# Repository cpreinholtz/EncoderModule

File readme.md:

# Overview - Dorthy - Digital Rotary Encoder based Teensy Synth
This repo contains several PCB designs and teensy firmware for building a digital sythesiser.

**Directory structure:**
* cad (empty...)
* doc (mostly datasheets and links to research sources)
* firmware (arduino sketches)
* hardware (eagle projects)
* production (gerber zips)
* simulation (empty...)

**PCBs (see detailed descriptions below)**
* **R**otary **E**ncoder **E**xpander **M**odule (REEM)
* **G**round **I**solated **M**idi **I**nput Module (GIMI)
* **D**igital **R**otary Encoder **T**eensy S**y**nth (DRTY / DORTHY)

## Rotary Encoder Expander Module (REEM)

### Overview

This module is meant to be an expandable way to attach many rotary encoders to a single i2c master.  The idea is that it can be used in creating a nice user interface for a synthesizer.  This project is meant to be small, to keep manufacturing costs down, but also expandable so that multiple of these can be connected together to make a large io pannel. Currently limited to 8 modules or 64 knobs based on the io expander chip used.

### Hardare Features

* Voltage input 1.8 — 5.5 V
* Optional pullups on SCL and SDA, do not pupulate by default,  should be pulled up on master side.
* Chainable design, simply connect modules using the ribbon cable connectors. (VCC, GND, SCL, SDA).
* 3 address pins per chip allow up to 8 unique addresses.  
 * **The address pins are floating by default and must be tied to vcc or ground by shorting one of the two 0805 resitor pads per pin**

### Future Considerations
* If you want chainable interupts, its probably possible, especially with more io lines on the chips
* it may be nice to someday take advantage of the switches built into the encoders, but i thought i would skip for now
* Optional hardware filter circuits for each encoder might improve performance but would mean more soldering
* Instead of an encoder, We could allow switches or buttons in the same form factor.
* Consider a form factor that fits with eurorack standards.
 * The Eurorack format calls for modules of 128.5mm (slightly over 5") height. Horizontal width is measured in "horizontal pitch", where 1 HP = 5.08mm (exactly 0.2").  This is larger than eagle free can build and fab houses may charge more 
* I wonder if it would be cheaper to use JST connectors for board to board connections.  See adafruit Trellis for example.

## **G**round **I**solated **M**idi **I**nput Module (GIMI)

### 

### Overview
Classic octocoupler used for midi digitization for arduino or similar controllers.

***Warning ***
In rev 1 of producing this baord the M4 and M5 pin labels were swapped on the silkscreen.  Refer to the schematic and drawings, not the silkscreen.

### Hardare Features
* reverse polarity protection diode.
* midi in uses octocoupler preventing ground loops.  
* RX pullup does not need to be 5v.  Can be tied to 3v3, or whatever voltage the controller needs.
* Jumper for quickly disconnecting RX from the circuit.  For re-programming certain controllers Rx may need to be floating.

### Future Considerations
* It would be pretty easy to add midi through and/or midi out at some point.
* It may be nice to get board mount midi connectors at some point.
* It may be nice to start using a standard cable (like JST SH or JST PH...) rather than the 100mil pitch headers I put on.

## Dorthy Teensy Synth (work in progress)
Designed around a teensy microcontroller and some other hardware modules.  Utilizes the teensy audio libraries and some custom firmware.

### Playing the Synth
Instructions and features tbd.

## Dorthy Teensy Synth Hardare 
Take a teensy, slap 64 knobs and 16 buttons onto it, make it midi compatable and make some music

#### BOM
* 1x Teensy microcontroller, at least Rev 3.5 reccomended.
* 1x Midi in GIMI module (hardware/midi_in)
* 8x REEM modules(hardware/MultiEncoder)
* 2x large capacitors for stereo audio out, simple bypass cap to bring it to 0v centered.
* LCD display? tbd
* trellis? https://www.adafruit.com/product/3954

#### Hardware Pinouts
TBD

## Dorthy Teensy Synth Firmware
This synth will make heavy use of the teensy audio libraries and other goodies found all over the web.  Special thanks to all the contributors!

#### Firmware Detailed Descriptions (Requirments...)
* Polled processes: knobs(>100Hz), capacitive touch pads(100Hz?), midi RX(Every loop), Trellis (100Hz?), Clock Monitor(Every Loop), Touchscreen(100Hz?)
* While polling, if something is found that requires updates, the dispatcher class is called.
* When called the dispatcher will perform one or more actions such as modifying the voices or other synth parameters, and updating the display.
* The synth itself will have N voices, each with its own oscilators, LFOs?, amplitude envelope, filter and filter envelope.
* The synth will then combine all voices and send them through an effects signal chain containing delay, reverb, bitcrush, etc.
* The synth will respond to pitch bending and modwheel messages.
* The synth will be able to store up to M "note on" messages at a time, and will use the LAST N notes on the voices, upon notoffs it will go back through the list in revers chronological order.

#### Firmware Immediate Todo List
* Test what happens if the SetScalers function is passed a max smaler than min, hopefully it just reverses the knob polarity, that would be sweet
* Rewrite Midi function so that it does not take 50 ms to exxecute...
* Figure out why polyphonic note off does not often continue the release envelope if another note is hit.

#### Firmware Future Considerations
* It would be nice to have a good sequencer in the future, (keep this in mind when writing the dispatcher and voice controls)  consider things like kbd play / stack live 
* It would be nice to have a built in drum machine in the future.
* It would be nice to have the ability to save patches.  (make settings easy to get / set)
* It would be nice to be able to swap LFOs from incremental clk sync to continuous bpm sweeps.  this requires some back and forth from dispatcher to clk and lfo.
* It would be nice to be able to swap from re-triggering envelopes on each additional key to using one envelop for all voices(more smooth /legatto)

#### Firmware Enviromental setup
All you should need is arduino IDE with the teensy 3.6 board installed.
Teensy 1.53 seems to work much faster than the latest versions, Note to self: I have a copy of the 1.53 installer on my google drive main folder "installexes.rar" 
Arduino 1.8.13 works with this version of Teensy, I think I had issues with 1.8.16 and that teensy version.

#### Firmware Dependencies
must have https://github.com/cpreinholtz/midi.git   installed in Docs/Arduino/Libraries, look at the dates, its being developed in tandem but for now the latest woriking commit is 7a53122

#### Firmware Limitations
TBD

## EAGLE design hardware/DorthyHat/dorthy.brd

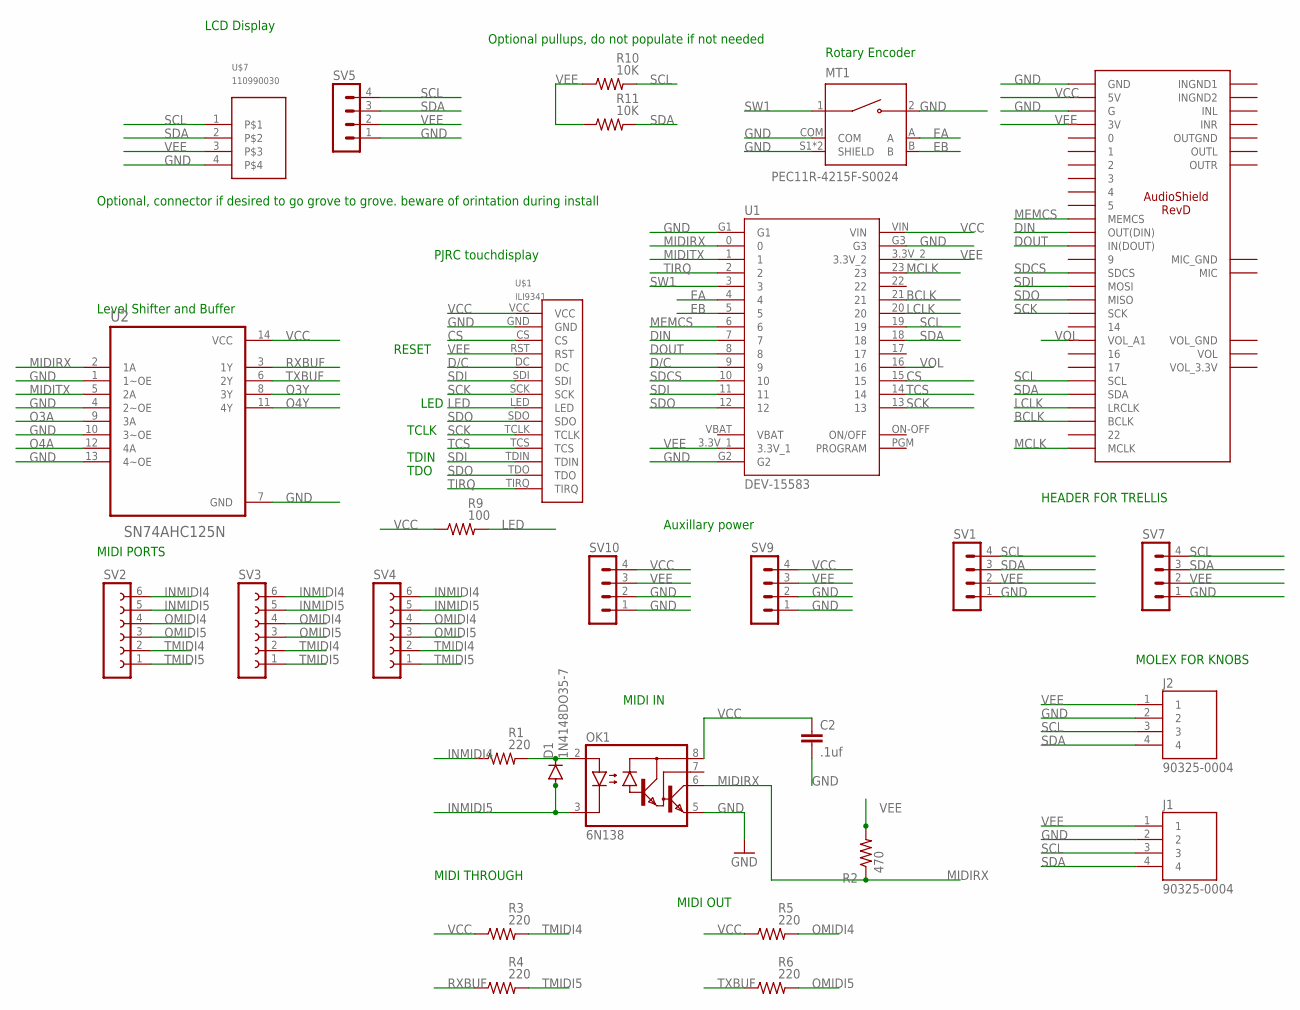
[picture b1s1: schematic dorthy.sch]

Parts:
C2: .1uf; C5B3.5
D1: 1N4148DO35-7; DO35-7
J1, J2: 90325-0004; MOLEX_90325-0004
MT1: PEC11R-4215F-S0024; XDCR_PEC11R-4215F-S0024
OK1: 6N138; DIL08
R1, R3, R4, R5, R6: 220; 0207/10
R2: 470; 0207/10
R9: 100; 0207/10
R10, R11: 10K; 0207/10
SV1, SV5, SV7, SV9, SV10: MA04-1
SV2, SV3, SV4: FE06-1; FE06
U1: DEV-15583; MODULE_DEV-15583
U2: SN74AHC125N; DIP794W45P254L1969H508Q14
U$1: ILI9341
U$2: AUDIOSHIELD-REVD
U$7: 110990030; 110990030-VERTICAL-GROVE-CONNECTOR

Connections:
BCLK: U1.21, U$2.21 (BCLK)
CS: U1.15, U$1.CS
D/C: U1.9, U$1.DC
DIN: U1.7, U$2.7 (OUT(DIN))
DOUT: U1.8, U$2.8 (IN(DOUT))
EA: MT1.A, U1.4
EB: MT1.B, U1.5
GND: C2.2, J1.2, J2.2, MT1.2, MT1.COM, MT1.S1 (SHIELD), MT1.S2 (SHIELD), OK1.5 (GND), SV1.1, SV5.1, SV7.1, SV9.1, SV9.2, SV10.1, SV10.2, U1.G1, U1.G2, U1.G3, U2.1 (1~OE), U2.4 (2~OE), U2.7 (GND), U2.10 (3~OE), U2.13 (4~OE), U$1.GND, U$2.G, U$2.GND, U$7.4
INMIDI4: R1.1, SV2.6, SV3.6, SV4.6
INMIDI5: D1.A, OK1.3 (C), SV2.5, SV3.5, SV4.5
LCLK: U1.20, U$2.20 (LRCLK)
LED: R9.2, U$1.LED
MCLK: U1.23, U$2.23 (MCLK)
MEMCS: U1.6, U$2.6 (MEMCS)
MIDIRX: OK1.6 (VO), R2.1, U1.0, U2.2 (1A)
MIDITX: U1.1, U2.5 (2A)
unnamed: D1.C, OK1.2 (A), R1.2
O3A: U2.9 (3A)
O3Y: U2.8 (3Y)
O4A: U2.12 (4A)
O4Y: U2.11 (4Y)
OMIDI4: R5.2, SV2.4, SV3.4, SV4.4
OMIDI5: R6.2, SV2.3, SV3.3, SV4.3
RXBUF: R4.1, U2.3 (1Y)
SCK: U1.13, U$1.SCK, U$1.TCLK, U$2.13 (SCK)
SCL: J1.3, J2.3, R10.2, SV1.4, SV5.4, SV7.4, U1.19, U$2.19 (SCL), U$7.1
SDA: J1.4, J2.4, R11.2, SV1.3, SV5.3, SV7.3, U1.18, U$2.18 (SDA), U$7.2
SDCS: U1.10, U$2.10 (SDCS)
SDI: U1.11, U$1.SDI, U$1.TDIN, U$2.11 (MOSI)
SDO: U1.12, U$1.SDO, U$1.TDO, U$2.12 (MISO)
SW1: MT1.1, U1.3
TCS: U1.14, U$1.TCS
TIRQ: U1.2, U$1.TIRQ
TMIDI4: R3.2, SV2.2, SV3.2, SV4.2
TMIDI5: R4.2, SV2.1, SV3.1, SV4.1
TXBUF: R6.1, U2.6 (2Y)
VBAT: U1.VBAT
VCC: C2.1, OK1.8 (VCC), R3.1, R5.1, R9.1, SV9.4, SV10.4, U1.VIN, U2.14 (VCC), U$1.VCC, U$2.5V
VEE: J1.1, J2.1, R2.2, R10.1, R11.1, SV1.2, SV5.2, SV7.2, SV9.3, SV10.3, U1.3.3V_1, U1.3.3V_2, U$1.RST, U$2.3V, U$7.3
VOL: U1.16, U$2.15 (VOL_A1)

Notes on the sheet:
Optional pullups, do not populate if not needed
MIDI THROUGH
MIDI OUT
MIDI IN
MOLEX FOR KNOBS
HEADER FOR TRELLIS
MIDI PORTS
Level Shifter and Buffer
PJRC touchdisplay
LED
RESET
TCLK
TDIN
TDO
Rotary Encoder
Auxillary power
LCD Display
Optional, connector if desired to go grove to grove. beware of orintation during install

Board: 2 copper layers, 28 parts (0 on the bottom side), 35 nets, no tracks yet.

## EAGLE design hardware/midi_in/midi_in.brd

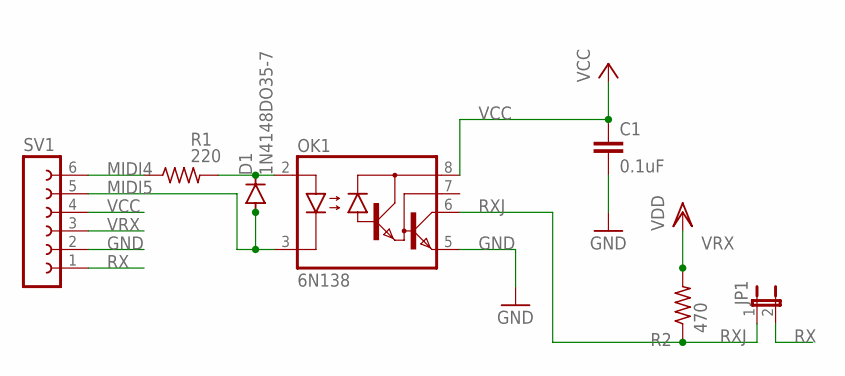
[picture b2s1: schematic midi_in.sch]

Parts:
C1: 0.1uF; C10B5
D1: 1N4148DO35-7; DO35-7
JP1: JP1E; JP1
OK1: 6N138; DIL08
R1: 220; 0207/10
R2: 470; 0207/10
SV1: FE06-1; FE06

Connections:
GND: C1.2, OK1.5 (GND), SV1.2
MIDI4: R1.1, SV1.6
MIDI5: D1.A, OK1.3 (C), SV1.5
unnamed: D1.C, OK1.2 (A), R1.2
RX: JP1.2, SV1.1
RXJ: JP1.1, OK1.6 (VO), R2.1
VCC: C1.1, OK1.8 (VCC), SV1.4
VRX: R2.2, SV1.3

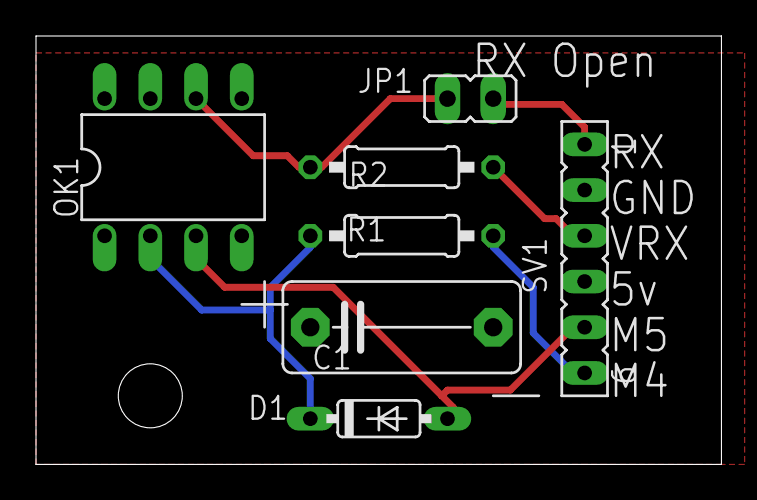
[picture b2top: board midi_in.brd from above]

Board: 2 copper layers, 38.1 x 23.8 mm, 7 parts (0 on the bottom side), 8 nets.

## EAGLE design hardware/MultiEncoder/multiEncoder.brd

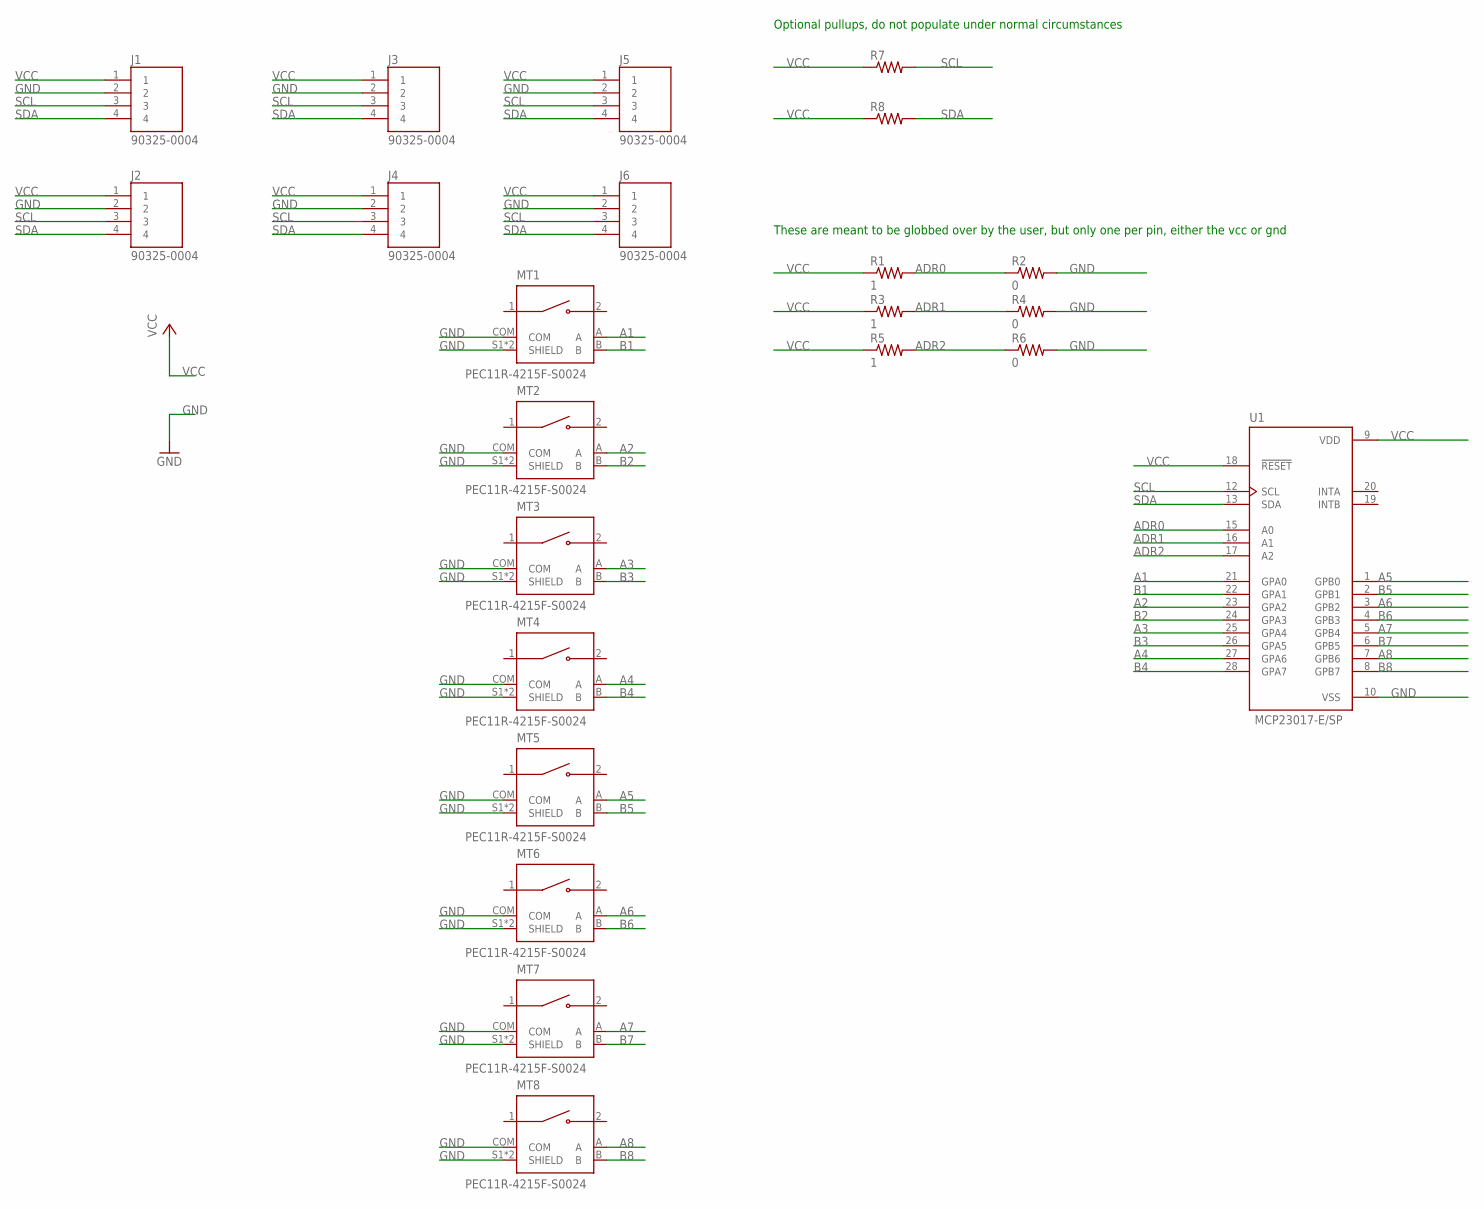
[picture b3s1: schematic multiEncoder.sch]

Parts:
J1, J2, J3, J4, J5, J6: 90325-0004; MOLEX_90325-0004
MT1, MT2, MT3, MT4, MT5, MT6, MT7, MT8: PEC11R-4215F-S0024; XDCR_PEC11R-4215F-S0024
R1, R3, R5: 1; R0805
R2, R4, R6: 0; R0805
R7, R8: 1K; R0805
U1: MCP23017-E/SP; DIP787W45P254L3556H508Q28

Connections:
A1: MT1.A, U1.21 (GPA0)
A2: MT2.A, U1.23 (GPA2)
A3: MT3.A, U1.25 (GPA4)
A4: MT4.A, U1.27 (GPA6)
A5: MT5.A, U1.1 (GPB0)
A6: MT6.A, U1.3 (GPB2)
A7: MT7.A, U1.5 (GPB4)
A8: MT8.A, U1.7 (GPB6)
ADR0: R1.2, R2.1, U1.15 (A0)
ADR1: R3.2, R4.1, U1.16 (A1)
ADR2: R5.2, R6.1, U1.17 (A2)
B1: MT1.B, U1.22 (GPA1)
B2: MT2.B, U1.24 (GPA3)
B3: MT3.B, U1.26 (GPA5)
B4: MT4.B, U1.28 (GPA7)
B5: MT5.B, U1.2 (GPB1)
B6: MT6.B, U1.4 (GPB3)
B7: MT7.B, U1.6 (GPB5)
B8: MT8.B, U1.8 (GPB7)
GND: J1.2, J2.2, J3.2, J4.2, J5.2, J6.2, MT1.COM, MT1.S1 (SHIELD), MT1.S2 (SHIELD), MT2.COM, MT2.S1 (SHIELD), MT2.S2 (SHIELD), MT3.COM, MT3.S1 (SHIELD), MT3.S2 (SHIELD), MT4.COM, MT4.S1 (SHIELD), MT4.S2 (SHIELD), MT5.COM, MT5.S1 (SHIELD), MT5.S2 (SHIELD), MT6.COM, MT6.S1 (SHIELD), MT6.S2 (SHIELD), MT7.COM, MT7.S1 (SHIELD), MT7.S2 (SHIELD), MT8.COM, MT8.S1 (SHIELD), MT8.S2 (SHIELD), R2.2, R4.2, R6.2, U1.10 (VSS)
SCL: J1.3, J2.3, J3.3, J4.3, J5.3, J6.3, R7.2, U1.12 (SCL)
SDA: J1.4, J2.4, J3.4, J4.4, J5.4, J6.4, R8.2, U1.13 (SDA)
VCC: J1.1, J2.1, J3.1, J4.1, J5.1, J6.1, R1.1, R3.1, R5.1, R7.1, R8.1, U1.9 (VDD), U1.18 (!RESET)

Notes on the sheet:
These are meant to be globbed over by the user, but only one per pin, either the vcc or gnd
Optional pullups, do not populate under normal circumstances

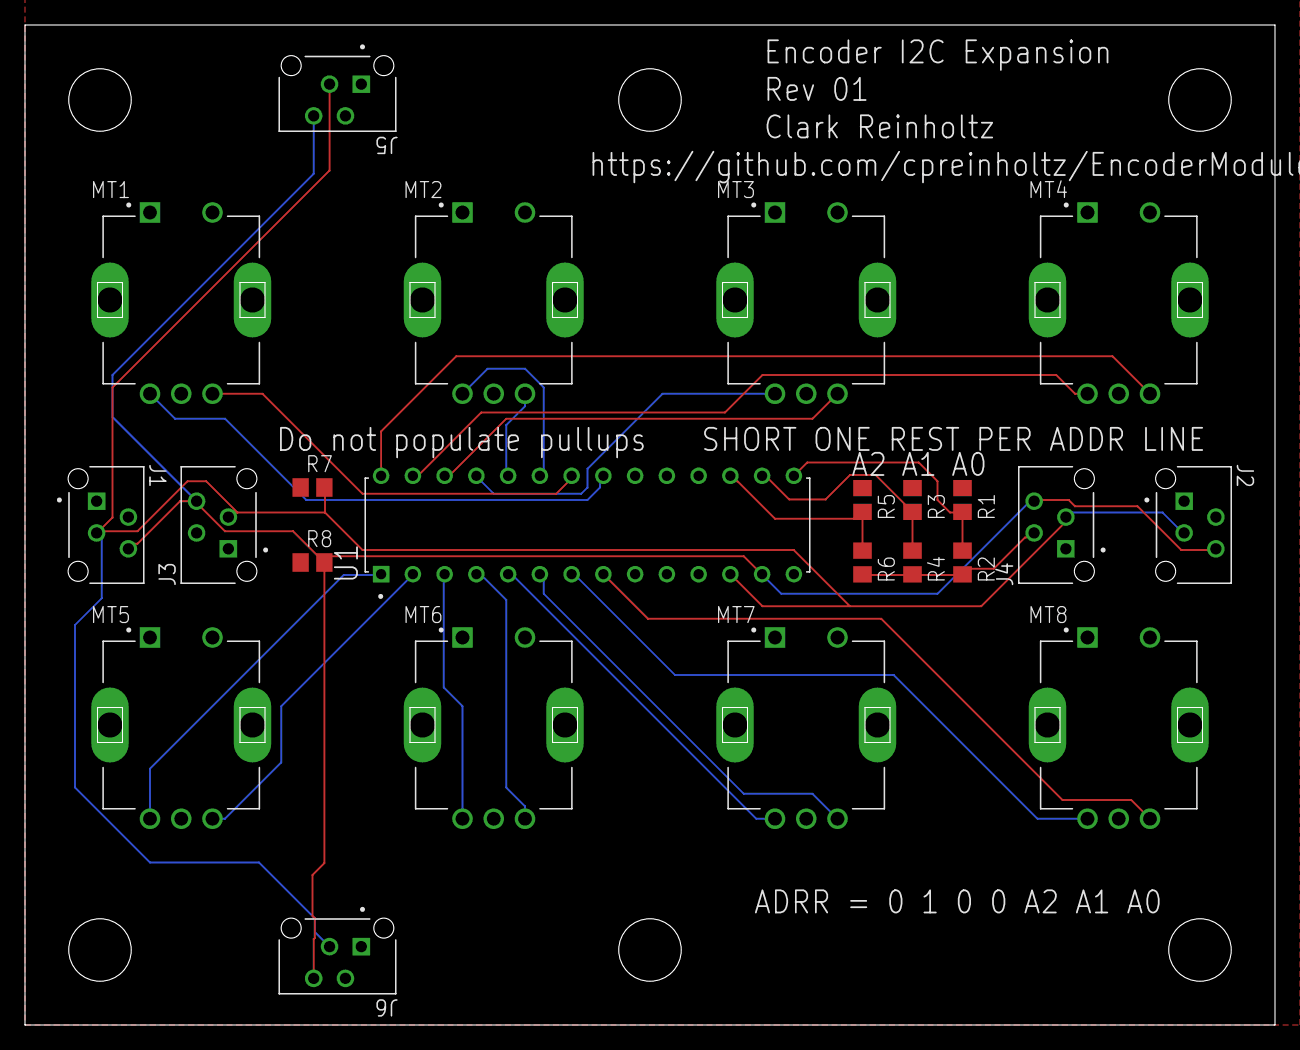
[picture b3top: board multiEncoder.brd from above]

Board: 2 copper layers, 100.0 x 80.0 mm, 23 parts (0 on the bottom side), 23 nets.

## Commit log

2021-10-08 inital commit
2021-10-08 change to 8 knob per module, 64 knob max
2021-10-08 Parts are placed, add ploygons and optional i2c line pullups
2021-10-08 run autorouter on all signals beddides addr lines
2021-10-08 All signals routed, ERC and DRC passes, just need to check footprints really
2021-10-09 Switch to a dip package for the ioexpander chip, re route signals
2021-10-09 fix an unrouted net
2021-10-09 save project file
2021-10-09 add vertical connection option
2021-10-09 project save
2021-10-09 Add identifying markings to silkscreen
2021-10-09 Add gerber zipfile
2021-10-09 move addr1 line away from addr0 pad, regenerate gerbers
2021-10-09 add midi input module
2021-10-11 swap M4 and M5 silkscreen for midi in. Big doccumentation update
2021-11-19 add initial schematic for the 'Dorthy' teensy sheild
2021-11-20 added touch screen lcd to dorthy, realized teensy 4.0 does not have true analog outputs, need to revert to 3.5 if I want simple outs...
2021-11-20 change to teensy 3.6. Add AGND for audio outs. Add power headers for future addons
2021-11-20 make board 100mmX100mm. add 9 capacitive touch pads. add rotary encoder... why not?
2021-11-21 add midi test sketch. The teensy + GIMI module are working with 5 pin midi in!
2021-11-22 add test sketch for a single knob, time to make this expandable to N knobs
2021-11-22 add object oriented implimentation of encoder motion tracking with the hope that is is easly expandable to multiple knobs in the future
2021-11-22 readme update
2021-11-22 readme
2021-11-22 rewirte midi notes class for polyphonic usage. compiles but still need to test
2021-11-23 add voice arbitration class
2021-11-23 note and voice arbitration is working
2021-11-24 start adding voice components
2021-11-24 teensy wont boot
2021-11-24 polyphonic play and pitchbending is working!
2021-11-24 start adding control logic for storing and setting audio settings
2021-11-25 knob polling first pass is working
2021-11-25 knob polling is working with 2 REEM modules
2021-11-27 knob polling works with up to 7 reems, 8 seems to be too much capacitance, todo, make logrithmic scaling for lfo bpm
2021-11-27 Added effect signal chain!
2021-11-28 rewrite voice and note arbitration for faster execution and better polyphonic behavior
2021-11-28 remove frequency LFO, trim signal before filter to minimize clipping, increase filter resonance limits, change a few other scalers
2021-11-28 add wavefolder
2021-12-23 use aduiosheild rather than built in DAc output. increase knob polling frequency to every 5 ms, runs well on teensy 4.0
2021-12-23 rearrange knobs and downsize to 4 reem modules. set rvb scaler to max .75 room size.
2021-12-23 minimum shp lfo set to 0.0 bpm (full stop)
2021-12-24 change shematic (back) to teensy 4.0, with audio sheild and touch display
2021-12-24 add custom footprint for the display
2021-12-24 start moving components around
2021-12-25 Component placement first pass finished for Dorthy
2021-12-25 add holes and polygons
2021-12-26 change triangle to square wave, volume to 1.0 on output
2021-12-26 replace reverb with flanger, code is messy for this hacky drop in
2022-03-18 readme arduino version 1.8.13
2022-10-15 Add chord_maker from my midi library at https://github.com/cpreinholtz/midi.git
2022-10-24 adding midi middleman, chordmaker works, currently testing arpegio
2022-11-04 fix some of the behavioral errors introduced by adding the arpegio
2023-04-11 move dorthy
2023-04-11 Add code to save and load patches
2023-04-11 fix compile errors
2023-04-11 add glide to code (untested and not a true logrithmic)
2023-04-11 fix glide bugs
2023-04-11 fix bugs in saving and loading patches
2023-04-12 add frequency drift code and ALSO REMOVE DEFAULTS ASSIGN FUNCT in favor of eeprom
2023-04-12 dammm this sounds cool
2023-04-13 add key to eeprom and a dummy lock for saving and loading, also added delay panning lfo
2023-04-17 add toggle options for glide from closest, clk div for lfos, mod wheel and aftertouch destinations, add audio settings to patch saving
2023-04-18 make 6 voice, fix bugs from the features in previous commit
